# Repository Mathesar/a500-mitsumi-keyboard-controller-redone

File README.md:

# Mitsumi PCB A-500 redone

This is a remake ("redone") of the Amiga 500 Mitsumi keyboard controller.

The original Amiga 500 uses a MOS 6570 microcontroller that is no longer produced and therefore getting exceedingly rare. They are also starting to fail, resulting in the dreaded "blinking CAPS-LOCK" issue. Since there was no open-source / open-hardware replacement design available I decided to make my own.

This is a completely new "from scratch" design that uses a Microchip [PIC18F4520](https://www.microchip.com/en-us/product/pic18f4520) microcontroller. I chose this type as it is available in a DIP40 package that is easy to solder by hand. It also gives this new redone keyboard controller a very similar look like the original controller. 

Lastly, what I like about the PIC18F4520 is that it is an 8bit microcontroller with modest capabilities not unlike the MOS 6570. It would bother me a bit to use a 50MHz+ 32bit ARM processor that is magnitudes faster than the Amiga's 68000 CPU just to scan a keyboard.

## Features

* Completely independent design.
* Fully compatible with the original Mitsumi keyboard controller.
* Debouncing filter.
* Anti-ghosting filter.
* Dimming power LED that also works on older Amiga 500 motherboard revisions.
* Through-hole design using currently available components for a retro look.
* Uses three 5mm x 2mm x 7mm LEDs instead of the unobtanium Commodore 15mm LED.
* Optionally, a 3D printed lightguide can be used to give a cleaner LED look.

## Molex ZIF connector

The original keyboard controller uses a Molex right angle ZIF connector to connect to the keyboard matrix membrane. This connector is very hard (impossible?) to get. I therefore used the straight version of this connector, the [Molex 39-53-2315](https://www.molex.com/en-us/products/part-detail/39532315). This connector is soldered on the edge of the circuitboard. This causes the entry point of the connector to sit lower than the original. This puts some strain on the flat cable and one should therefore take care when assembling the keyboard.

## LED brightness tuning

Modern LEDs are way brighter than the LEDs that Commodore used back in the days.
If the LEDs turn out too bright, they can be tuned by changing some resistor values.

### Drive LED

The drive LEDs can be tuned by simply changing resistor R12. Higher values lower the brightness.

### Power LED

The power LEDs are a bit special. One cannot simply use a larger than original current limiting resistor. This is because of the power LED dimming function on later revisions of the Amiga 500. Simply using a larger current limiting resistor would make the dimming hardly noticeable causing the power LEDs to always shine at seemingly full brightness.

To solve this, the circuit around Q1/Q2 has been added. This circuit detects when the LEDs should be dimmed or not. If the Amiga turns the LEDs on (full brightness on later revisions), only Q2 will conduct and deliver current to the LEDs via both R10 and R11. When the Amiga turns the LEDs off (dimmed on later revisions), only Q1 will conduct and current to the LEDs is only delivered via R10. The power LEDs will be dimmed.

For a good dimming effect, R10 should be about 4 times bigger than R11. This gives a current ratio of about 1:5.
In order to reduce or increase the brightness both resistors should thus be changed. Higher values lower the brightness.

## Building

The board is a completely through-hole design and should thus be easy to build. 
The BOM contains some partnumbers for the resistors but one can use any brand. None of the components are critical.

For the LEDs one can use 3 5mm x 2mm LEDs. These are still available. The top of these LEDs should sit above 12.3mm above the PCB. 
Alternatively, 3mm ("flat top") LEDs can be used combined with a 3D printed light guide. I had mine printed by JLC3DP using the 8001 "translucent" resin. The LEDs should be soldered close to the PCB to make this fit. Be aware though that the 8001 resin is not UV resistant on the long term. However, so far my light guides are holding up well.

To connect the keyboard controller to the main board a 300mm 8pin DuPont cable assembly can be used. The pinheader for this cable has 10 pins instead of 8. The extra pins are "auxiliary" pins meant for future expansions and not currently implemented. Therefore connect the keyboard cable only to pins 1..8 as indicated by the arrow.

## Firmware and programming

The firmware was developed using [MPLAB X ide v6.25](https://www.microchip.com/en-us/tools-resources/develop/mplab-x-ide).
The code is written in C for the [XC8 compiler](https://www.microchip.com/en-us/tools-resources/develop/mplab-xc-compilers/xc8).
These tools are freely available from [Microchip](https://www.microchip.com).

## Pictures

Picture of lightguide version mounted on an mechanical keyboard. The drive lightpipe has been removed to show the 3 flat top 3mm LEDs. You can also see how the groundstrap is supposed to connect. 

Render of version using three 5mm x 2mm LEDs

Closeup of version with 5mm x 2mm LEDs. On this picture I glued the LEDs together using an UV curable glue. These LEDs were originally fully transparant but I sanded the tops with sandpaper to get a more diffuse look.

## Licenses

The hardware is licensed under [CERN OHL-S V2.0](https://cern-ohl.web.cern.ch/).
The firmware is licensed under [GNU GPL V3](https://www.gnu.org/licenses/gpl-3.0.en.html).

## Acknowledgements

The KiCad keyboard schematic symbol was originally done by [Scott Lawrence](https://github.com/BleuLlama/AmigaSchematics/tree/master/A500_kyb_Mitsumi).

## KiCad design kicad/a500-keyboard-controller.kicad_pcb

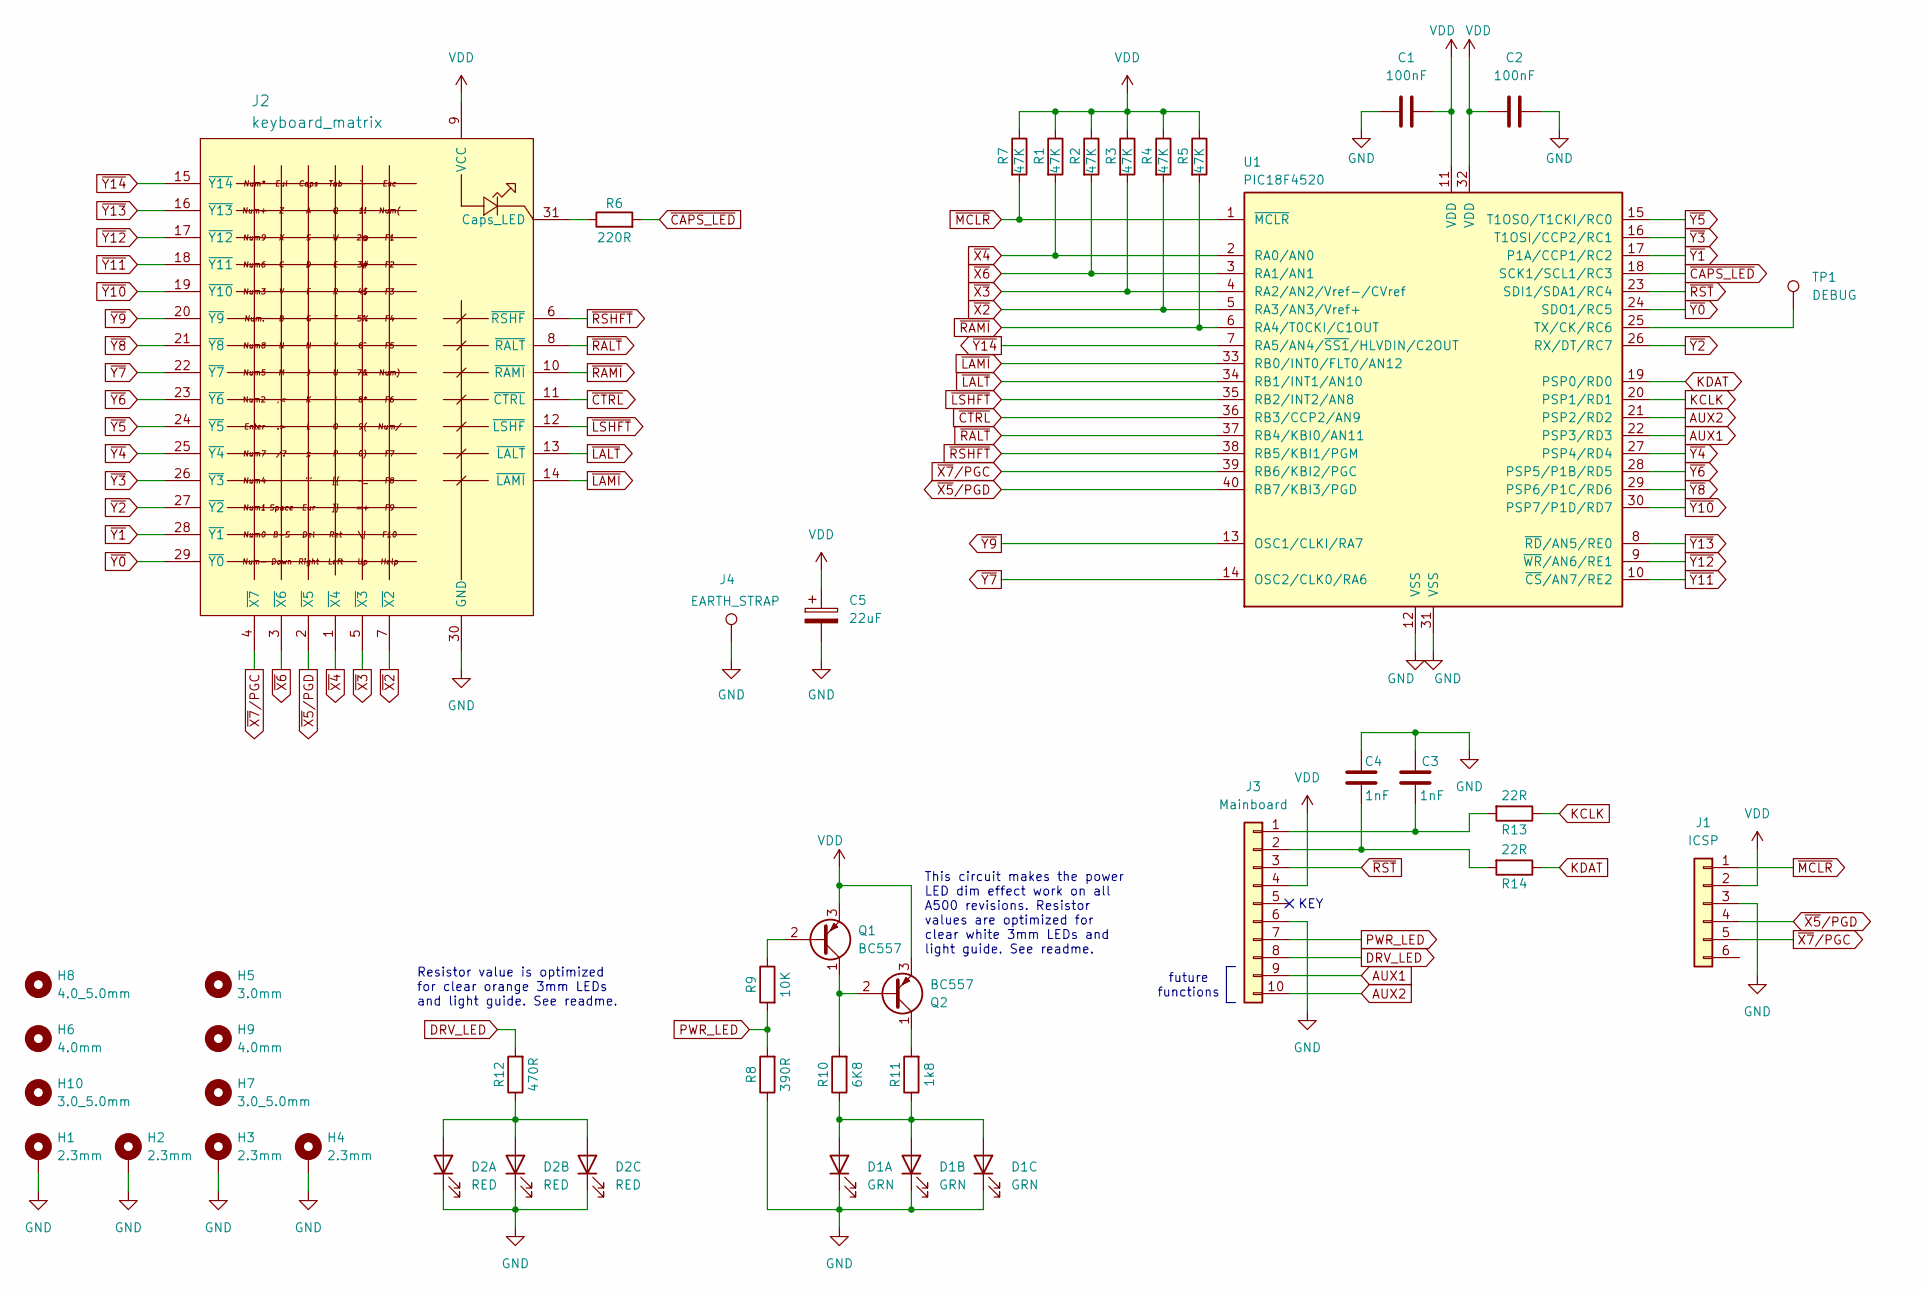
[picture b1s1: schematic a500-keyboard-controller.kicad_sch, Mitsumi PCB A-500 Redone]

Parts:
C1, C2: 100nF; C_Axial_L3.8mm_D2.6mm_P7.50mm_Horizontal; MPN A104K15X7RF5UAA
C3, C4: 1nF; C_Disc_D4.3mm_W1.9mm_P5.00mm; MPN D102K20Y5PH63J5R
C5: 22uF; CP_Radial_D6.3mm_P2.50mm; MPN EEA-GA1C220H
D1: GRN; A500_triple_LED_equivalent
D2: RED; A500_triple_LED_equivalent
H1, H2, H3, H4: 2.3mm; MountingHole_2.3mm_Pad
H5: 3.0mm; MountingHole_3mm
H6, H9: 4.0mm; MountingHole_4mm
H7, H10: 3.0_5.0mm; mountinghole_3.0_5.0
H8: 4.0_5.0mm; mountinghole_4.0_5.0
J1: ICSP; PinHeader_1x06_P2.54mm_Vertical
J2: keyboard_matrix; 39-53-2315; MPN 39-53-2315
J3: Mainboard; PinHeader_1x10_P2.54mm_Horizontal
J4: EARTH_STRAP; SolderWire-1.5sqmm_1x01_D1.7mm_OD3mm
Q1, Q2: BC557; TO-92_HandSolder_modified
R1, R2, R3, R4, R5, R7: 47K; R_Axial_DIN0207_L6.3mm_D2.5mm_P10.16mm_Horizontal; MPN MF0207FTE52-47K
R6: 220R; R_Axial_DIN0207_L6.3mm_D2.5mm_P10.16mm_Horizontal; MPN MF0207FTE52-220R
R8: 390R; R_Axial_DIN0207_L6.3mm_D2.5mm_P10.16mm_Horizontal; MPN MF0207FTE52-390R
R9: 10K; R_Axial_DIN0207_L6.3mm_D2.5mm_P10.16mm_Horizontal; MPN MF0207FTE52-10K
R10: 6K8; R_Axial_DIN0207_L6.3mm_D2.5mm_P10.16mm_Horizontal; MPN MF0207FTE52-6K8
R11: 1k8; R_Axial_DIN0207_L6.3mm_D2.5mm_P10.16mm_Horizontal; MPN MF0207FTE52-1K8
R12: 470R; R_Axial_DIN0207_L6.3mm_D2.5mm_P10.16mm_Horizontal; MPN MF0207FTE52-470R
R13, R14: 22R; R_Axial_DIN0207_L6.3mm_D2.5mm_P10.16mm_Horizontal; MPN MF0207FTE52-22R
TP1: DEBUG; TestPoint_THTPad_D2.0mm_Drill1.0mm
U1: PIC18F4520; DIP-40_W15.24mm; MPN PIC18F4520-I/P

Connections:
AUX1: J3.9, U1.22 (PSP3/RD3)
AUX2: J3.10, U1.21 (PSP2/RD2)
DRV_LED: J3.8, R12.2
GND: C1.1, C2.2, C3.2, C4.2, C5.2, D1.1 (K), D1.3 (K), D1.5 (K), D2.1 (K), D2.3 (K), D2.5 (K), H1.1, H2.1, H3.1, H4.1, J1.3, J2.30 (GND), J3.6, J4.1, R8.1, U1.12 (VSS), U1.31 (VSS)
KCLK: R13.1, U1.20 (PSP1/RD1)
KDAT: R14.1, U1.19 (PSP0/RD0)
unnamed: D1.2 (A), D1.4 (A), D1.6 (A), R10.1, R11.1
unnamed: D2.2 (A), D2.4 (A), D2.6 (A), R12.1
unnamed: J2.31 (Caps_LED), R6.1
unnamed: C3.1, J3.1, R13.2
unnamed: C4.1, J3.2, R14.2
unnamed: Q1.2 (B), R9.1
unnamed: Q1.1 (C), Q2.2 (B), R10.2
unnamed: Q2.1 (C), R11.2
unnamed: TP1.1, U1.25 (TX/CK/RC6)
PWR_LED: J3.7, R8.2, R9.2
VDD: C1.2, C2.1, C5.1, J1.2, J2.9 (VCC), J3.4, Q1.3 (E), Q2.3 (E), R1.1, R2.1, R3.1, R4.1, R5.1, R7.1, U1.11 (VDD), U1.32 (VDD)
~CAPS_LED: R6.2, U1.18 (SCK1/SCL1/RC3)
~CTRL: J2.11 (~CTRL), U1.36 (RB3/CCP2/AN9)
~LALT: J2.13 (~LALT), U1.34 (RB1/INT1/AN10)
~LAMI: J2.14 (~LAMI), U1.33 (RB0/INT0/FLT0/AN12)
~LSHFT: J2.12 (~LSHF), U1.35 (RB2/INT2/AN8)
~MCLR: J1.1, R7.2, U1.1 (~MCLR)
~RALT: J2.8 (~RALT), U1.37 (RB4/KBI0/AN11)
~RAMI: J2.10 (~RAMI), R5.2, U1.6 (RA4/T0CKI/C1OUT)
~RSHFT: J2.6 (~RSHF), U1.38 (RB5/KBI1/PGM)
~RST: J3.3, U1.23 (SDI1/SDA1/RC4)
~X2: J2.7 (~X2), R4.2, U1.5 (RA3/AN3/Vref+)
~X3: J2.5 (~X3), R3.2, U1.4 (RA2/AN2/Vref-/CVref)
~X4: J2.1 (~X4), R1.2, U1.2 (RA0/AN0)
~X5/PGD: J1.4, J2.2 (~X5), U1.40 (RB7/KBI3/PGD)
~X6: J2.3 (~X6), R2.2, U1.3 (RA1/AN1)
~X7/PGC: J1.5, J2.4 (~X7), U1.39 (RB6/KBI2/PGC)
~Y0: J2.29 (~Y0), U1.24 (SDO1/RC5)
~Y1: J2.28 (~Y1), U1.17 (P1A/CCP1/RC2)
~Y2: J2.27 (~Y2), U1.26 (RX/DT/RC7)
~Y3: J2.26 (~Y3), U1.16 (T1OSI/CCP2/RC1)
~Y4: J2.25 (~Y4), U1.27 (PSP4/RD4)
~Y5: J2.24 (~Y5), U1.15 (T1OSO/T1CKI/RC0)
~Y6: J2.23 (~Y6), U1.28 (PSP5/P1B/RD5)
~Y7: J2.22 (~Y7), U1.14 (OSC2/CLK0/RA6)
~Y8: J2.21 (~Y8), U1.29 (PSP6/P1C/RD6)
~Y9: J2.20 (~Y9), U1.13 (OSC1/CLKI/RA7)
~Y10: J2.19 (~Y10), U1.30 (PSP7/P1D/RD7)
~Y11: J2.18 (~Y11), U1.10 (~CS/AN7/RE2)
~Y12: J2.17 (~Y12), U1.9 (~WR/AN6/RE1)
~Y13: J2.16 (~Y13), U1.8 (~RD/AN5/RE0)
~Y14: J2.15 (~Y14), U1.7 (RA5/AN4/~SS1/HLVDIN/C2OUT)

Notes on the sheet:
KEY
future functions
Resistor value is optimized for clear orange 3mm LEDs and light guide. See readme.
This circuit makes the power LED dim effect work on all A500 revisions. Resistor values are optimized for clear white 3mm LEDs and light guide. See readme.

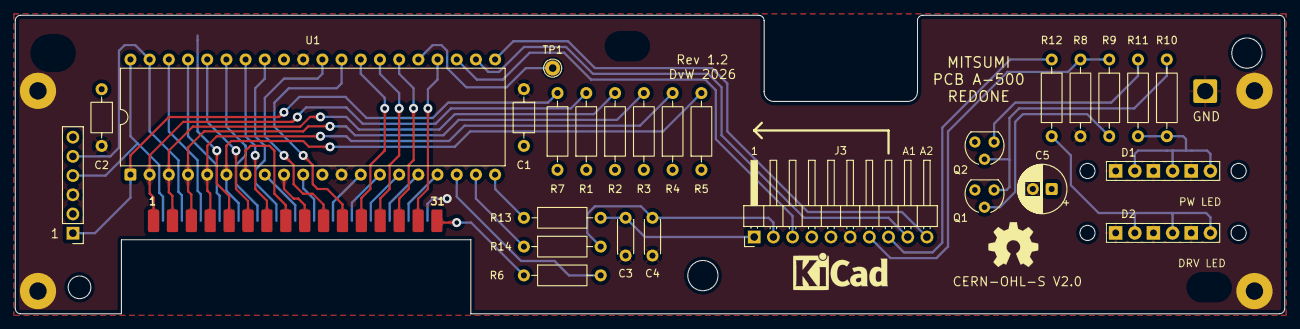
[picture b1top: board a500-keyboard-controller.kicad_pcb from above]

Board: 2 copper layers, 167.9 x 39.5 mm, 41 parts (0 on the bottom side), 48 nets.

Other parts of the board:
REF1: KiCad-Logo_5mm_SilkScreen
REF2: OSHW-Symbol_6.7x6mm_SilkScreen

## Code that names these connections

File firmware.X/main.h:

/*
 *  A500-Mitsumi-controller-redone firmware
 * 
 *  By Dennis van Weeren (2026)
 *  
 *  A500-Mitsumi-controller-redone is free software: you can redistribute it 
 *  and/or modify it under the terms of the GNU General Public License as 
 *  published by the Free Software Foundation, either version 3 of the License, 
 *  or (at your option) any later version.
 *
 *  This program is distributed in the hope that it will be useful,
 *  but WITHOUT ANY WARRANTY; without even the implied warranty of
 *  MERCHANTABILITY or FITNESS FOR A PARTICULAR PURPOSE.  See the
 *  GNU General Public License for more details.
 *
 *  You should have received a copy of the GNU General Public License
 *  along with A500-Mitsumi-controller-redone.  
 *  If not, see <https://www.gnu.org/licenses/>.
 */

#ifndef MAIN_H
#define	MAIN_H

// set below define to disable debugging
#define NDEBUG

#ifndef NDEBUG
#include <stdio.h>
#endif

// keyboard matrix row IO definitions
#define MATRIX_Y0       TRISCbits.TRISC5
#define MATRIX_Y1       TRISCbits.TRISC2
#define MATRIX_Y2       TRISCbits.TRISC7
#define MATRIX_Y3       TRISCbits.TRISC1
#define MATRIX_Y4       TRISDbits.TRISD4
#define MATRIX_Y5       TRISCbits.TRISC0
#define MATRIX_Y6       TRISDbits.TRISD5
#define MATRIX_Y7       TRISAbits.TRISA6
#define MATRIX_Y8       TRISDbits.TRISD6
#define MATRIX_Y9       TRISAbits.TRISA7
#define MATRIX_Y10      TRISDbits.TRISD7
#define MATRIX_Y11      TRISEbits.TRISE2
#define MATRIX_Y12      TRISEbits.TRISE1
#define MATRIX_Y13      TRISEbits.TRISE0
#define MATRIX_Y14      TRISAbits.TRISA5

// special key IO definitions
#define LEFT_AMIGA      PORTBbits.RB0
#define LEFT_ALT        PORTBbits.RB1
#define LEFT_SHIFT      PORTBbits.RB2
#define CTRL            PORTBbits.RB3
#define RIGHT_ALT       PORTBbits.RB4
#define RIGHT_SHIFT     PORTBbits.RB5
#define RIGHT_AMIGA     PORTAbits.RA4

// other IO
#define DEBUG           LATCbits.LATC6
#define KDAT_WRITE      TRISDbits.TRISD0
#define KDAT_READ       PORTDbits.RD0
#define KCLK            TRISDbits.TRISD1
#define CAPS_LOCK       LATCbits.LATC3
#define HOST_RESET      TRISCbits.TRISC4

// micro-second timer macro's, resolution=4us, max=255ms
#define us_timer_set(us)            {TMR1 = (uint16_t)(65536UL-(((us)+3UL)/4UL));PIR1bits.TMR1IF = 0;}
#define us_timer_expired()          (PIR1bits.TMR1IF)
#define us_timer_wait()             {while(!PIR1bits.TMR1IF);}

// shared timer macro's, resolution = 128us
#define timer_get()                 (TMR0)
#define ms_to_timer(ms)             (((uint32_t)ms*1000UL)/128UL)
typedef uint16_t timer_t;

#endif	/* MAIN_H */

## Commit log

2026-01-01 This version sent to fabrication
2026-01-02 updated BOM
2026-01-07 added MPLab firmware project, work in progress
2026-01-09 - fixed oscillator speed
    - added printf functionality via DEBUG pin
2026-01-11 keyboard scanning working via debug port
    ghost detection also working
    added untested host communication functions
2026-01-15 added main state machine
    refactored code
    added matrix to key code map
2026-01-17 added caps-lock handling
    fixed many small bugs
2026-01-17 fixed reset behaviour
    created proper defines for some constants
2026-01-18 - added watchdog
    - fixed bug in matrix_decode()
2026-01-18 fixed ghost detection algorithm
2026-01-21 modified shape for better hand solderability
2026-01-21 bigger footprint for bulk capacitor
    bumped revision
2026-01-21 larger margin around ground pads
    Moved ICSP connector
    added teardrops to SMD pads
    optimized some tracks so we can move host cable connector
2026-01-24 host cable now connects to right angle pin header
    This is version 1.1 and has been sent to production
2026-01-25 started on documentation
2026-01-26 some changes to documentation
2026-01-26 fixed image link
2026-01-30 removed compiler warning
    hand tuned keyboard comms timing for XC8 with -o2 optimizations @ 8MHz CPU speed
2026-02-01 added debounce logic
2026-02-01 fixed reset behavior
    general timer now has higher resolution
2026-02-02 added proper FIFO buffer for key codes
    matrix is now scanned faster
2026-02-04 improved debouncing code
2026-02-11 - fixed LED footprint dimensions
    - completely reworked power LED circuit
2026-02-11 moved OSHW logo a bit, this version sent to fabrication
2026-02-14 added FreeCAD model for lightpipe
2026-02-15 light pipe design for 2 LEDs
2026-03-07 changed LED current limiting resistors values
2026-03-07 added 3D model for lightguide
2026-03-08 Updated documentation and added pictures
2026-03-08 updated some resistor partnumbers
2026-03-08 some more documentation updates
